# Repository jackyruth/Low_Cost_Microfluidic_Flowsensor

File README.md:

# Low Cost Flowsensor
https://github.com/jackyruth/Low_Cost_Microfluidic_Flowsensor/assets/32418878/434e1281-520d-4bf3-973c-ca0241b3b97c

## Description
- Does the Job! Measures up to 80 uL/min
- Cheap! Has a BOM cost < 30CAD
- Accurate! 5% Median Accuracy < 55 uL/min, 10-18% Median Accuracy > 55uL/min
- Non-invasive! Wet components are standard 1/32' OD tygon tubing and 29G stainless steel
- Simple Interface! UART Outputs every 15 seconds

This project is also well documented:
- 'Flowsensor Product Specification.pdf': Datasheet for the flowsensor
- 'Flowsensor Requirements, Design & Verification.pdf': A document describing the requirements, design and verification of the flowsensor
- 'flowsensor_demonstration.MOV': A video showing the benchmarking process
- 'UBC_BioMEMS_Product_Video.mp4': A video describing the context of the system the flowsensor is originally designed to be a part of.

## Project Tree
```
.
├── data
├── julia
├── lsi_lab_validation
├── pcb_v1
├── README.md
├── reagent_compatibility
└── stm32
```

- 'data' contains time series temperature data measured at set flow rates
- 'julia' contains data science Pluto notebooks used to experiment with the time series temperature data and analyze benchmarking data 
- 'lsi_lab_validation' contains the benchmarking data where we pitted the low cost sensor against the Sensirion SLI-0430 FMK flowsensor
- 'pcb_v1' contains a KiCAD PCB project of the flowsensor
- 'reagent_compatibility' contains benchmarking data where we ran different reagents, some at different temperatures, through the flowsensor
- 'stm32' contains the firmware for the flowsensor

# License
The hardware design is licensed under CERN-OHL-P-2.0. All other components are licensed under Apache-2.0.

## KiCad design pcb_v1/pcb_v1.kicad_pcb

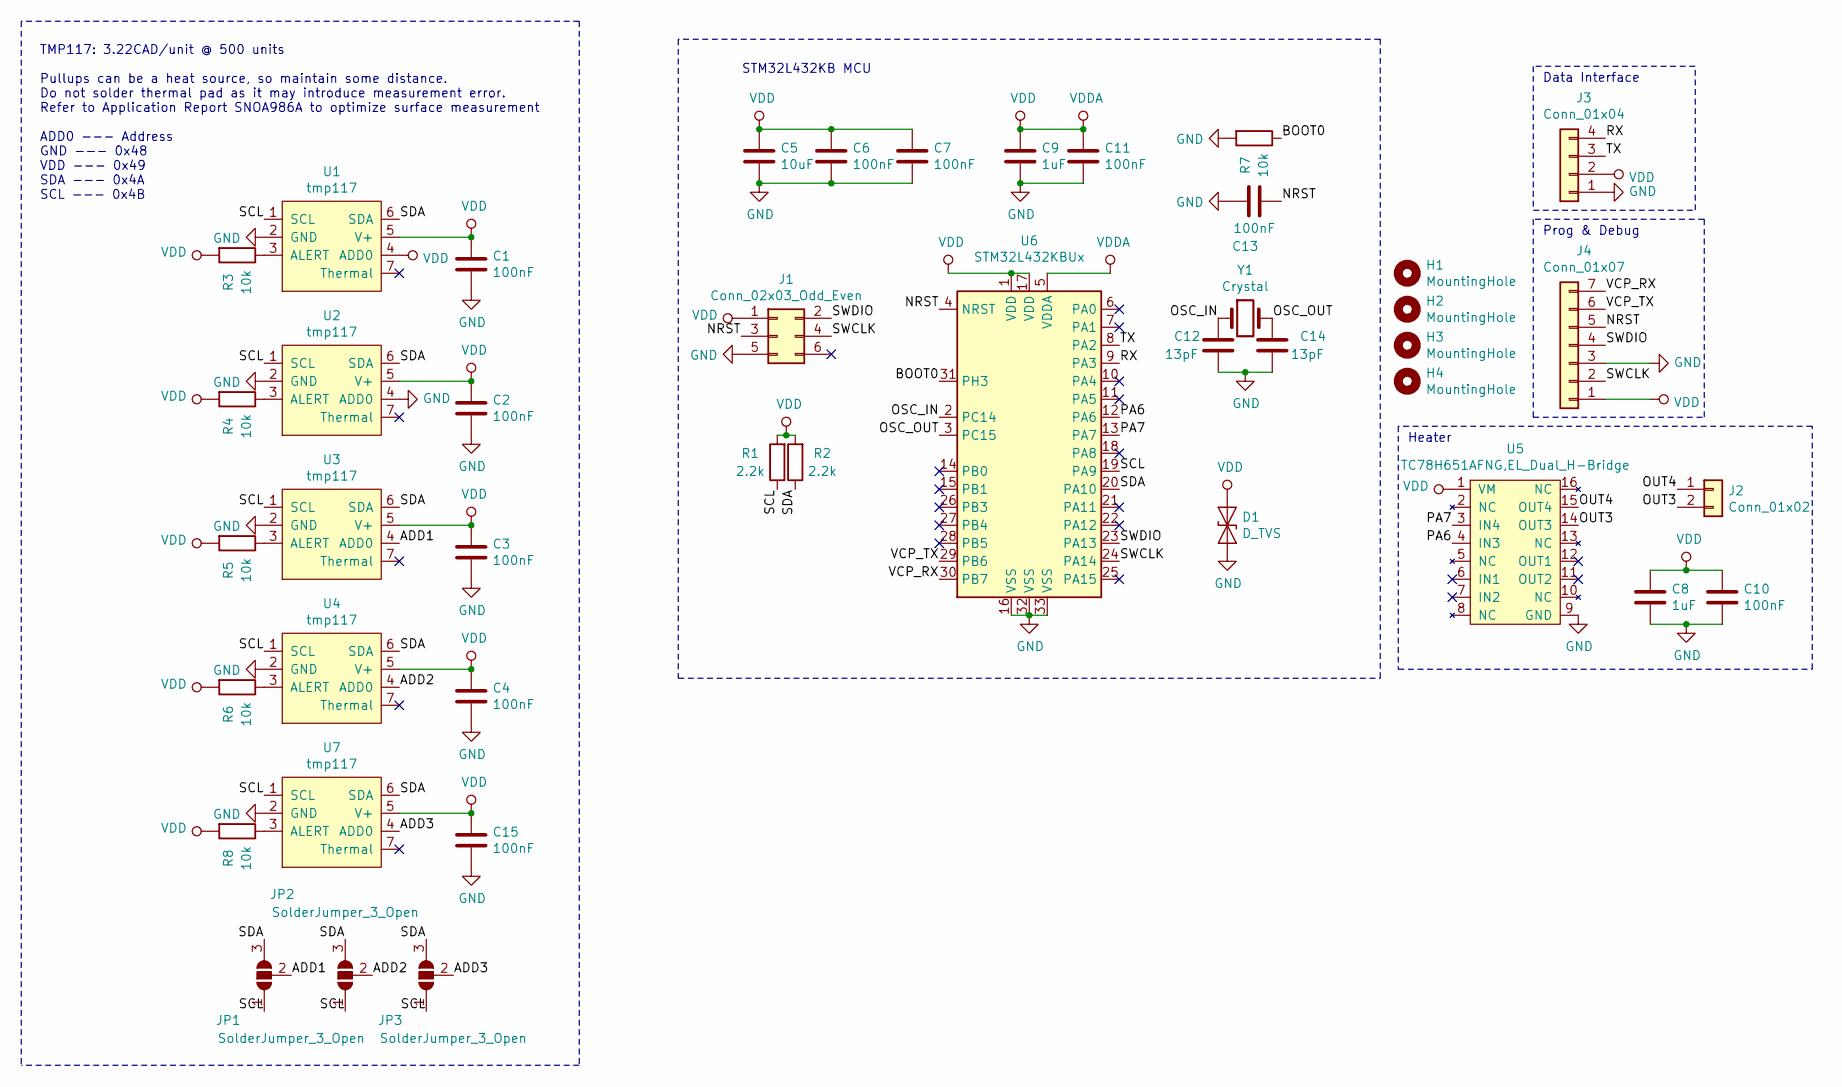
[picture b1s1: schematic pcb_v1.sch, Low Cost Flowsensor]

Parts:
C1, C2, C3, C4, C6, C7, C10, C11, C13, C15: 100nF; C_0603_1608Metric
C5: 10uF; C_0603_1608Metric
C8, C9: 1uF; C_0603_1608Metric
C12, C14: 13pF; C_0603_1608Metric
D1: D_TVS; D_SMA
H1, H2, H3, H4: MountingHole; MountingHole_2.2mm_M2
J1: Conn_02x03_Odd_Even; Tag-Connect_TC2030-IDC-NL_2x03_P1.27mm_Vertical
J2: Conn_01x02; R_Box_L8.4mm_W2.5mm_P5.08mm
J3: Conn_01x04; PinHeader_1x04_P2.54mm_Vertical
J4: Conn_01x07; PinHeader_1x07_P2.54mm_Vertical
JP1, JP2, JP3: SolderJumper_3_Open; SolderJumper-3_P1.3mm_Open_RoundedPad1.0x1.5mm_NumberLabels
R1, R2: 2.2k; C_0603_1608Metric
R3, R4, R5, R6, R7, R8: 10k; C_0603_1608Metric
U1, U2, U3, U4, U7: tmp117; THERMAL_ENHANCED_WSON-6-1EP_2x2mm_P0.65mm_EP1x1.6mm
U5: TC78H651AFNG,EL_Dual_H-Bridge
U6: STM32L432KBUx; QFN-32-1EP_5x5mm_P0.5mm_EP3.45x3.45mm
Y1: Crystal; ECS-.327-12.5-12R-C-TR

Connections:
/ADD1: JP1.2 (C), U3.4 (ADD0)
/ADD2: JP2.2 (C), U4.4 (ADD0)
/ADD3: JP3.2 (C), U7.4 (ADD0)
/BOOT0: R7.1, U6.31 (PH3)
/NRST: C13.2, J1.3, J4.5, U6.4 (NRST)
/OSC_IN: C12.2, U6.2 (PC14), Y1.1
/OSC_OUT: C14.2, U6.3 (PC15), Y1.2
/OUT3: J2.2, U5.14 (OUT3)
/OUT4: J2.1, U5.15 (OUT4)
/PA6: U5.4 (IN3), U6.12 (PA6)
/PA7: U5.3 (IN4), U6.13 (PA7)
/RX: J3.4, U6.9 (PA3)
/SCL: JP1.1 (A), JP2.1 (A), JP3.1 (A), R1.1, U1.1 (SCL), U2.1 (SCL), U3.1 (SCL), U4.1 (SCL), U6.19 (PA9), U7.1 (SCL)
/SDA: JP1.3 (B), JP2.3 (B), JP3.3 (B), R2.1, U1.6 (SDA), U2.6 (SDA), U3.6 (SDA), U4.6 (SDA), U6.20 (PA10), U7.6 (SDA)
/SWCLK: J1.4, J4.2, U6.24 (PA14)
/SWDIO: J1.2, J4.4, U6.23 (PA13)
/TX: J3.3, U6.8 (PA2)
/VCP_RX: J4.7, U6.30 (PB7)
/VCP_TX: J4.6, U6.29 (PB6)
GND: C1.1, C2.1, C3.1, C4.1, C5.2, C6.2, C7.2, C8.2, C9.2, C10.2, C11.2, C12.1, C13.1, C14.1, C15.1, D1.2 (A2), J1.5, J3.1, J4.3, R7.2, U1.2 (GND), U2.2 (GND), U2.4 (ADD0), U3.2 (GND), U4.2 (GND), U5.9 (GND), U6.16 (VSS), U6.32 (VSS), U6.33 (VSS), U7.2 (GND)
unnamed: R3.1, U1.3 (ALERT)
unnamed: R4.1, U2.3 (ALERT)
unnamed: R5.1, U3.3 (ALERT)
unnamed: R6.1, U4.3 (ALERT)
unnamed: R8.1, U7.3 (ALERT)
VDD: C1.2, C2.2, C3.2, C4.2, C5.1, C6.1, C7.1, C8.1, C9.1, C10.1, C11.1, C15.2, D1.1 (A1), J1.1, J3.2, J4.1, R1.2, R2.2, R3.2, R4.2, R5.2, R6.2, R8.2, U1.4 (ADD0), U1.5 (V+), U2.5 (V+), U3.5 (V+), U4.5 (V+), U5.1 (VM), U6.1 (VDD), U6.5 (VDDA), U6.17 (VDD), U7.5 (V+)

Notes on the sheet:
TMP117: 3.22CAD/unit @ 500 units Pullups can be a heat source, so maintain some distance. Do not solder thermal pad as it may introduce measurement error. Refer to Application Report SNOA986A to optimize surface measurement ADD0 --- Address GND --- 0x48 VDD --- 0x49 SDA --- 0x4A SCL --- 0x4B
STM32L432KB MCU
Prog & Debug
Data Interface
Heater

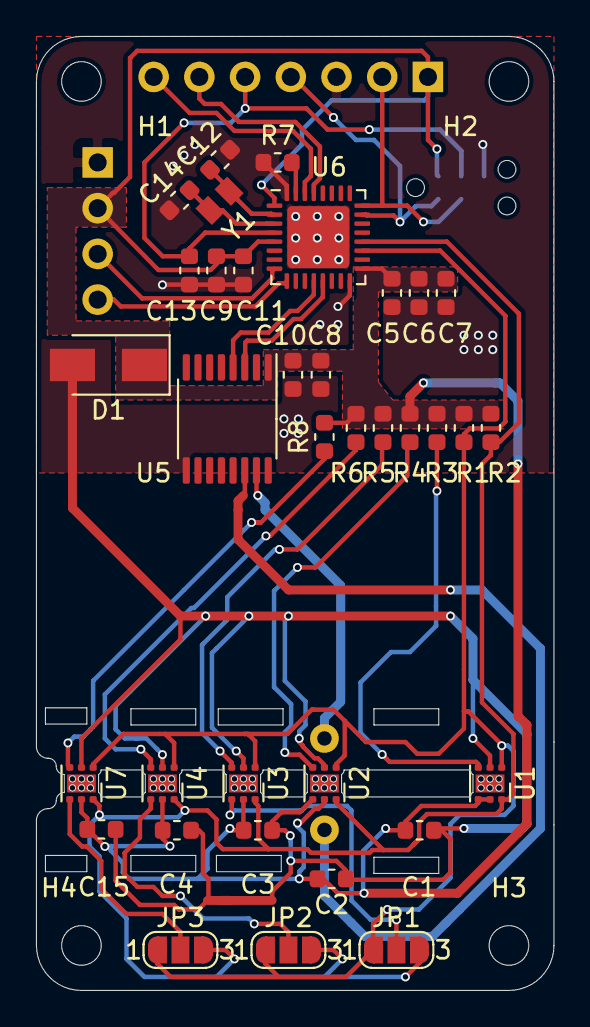
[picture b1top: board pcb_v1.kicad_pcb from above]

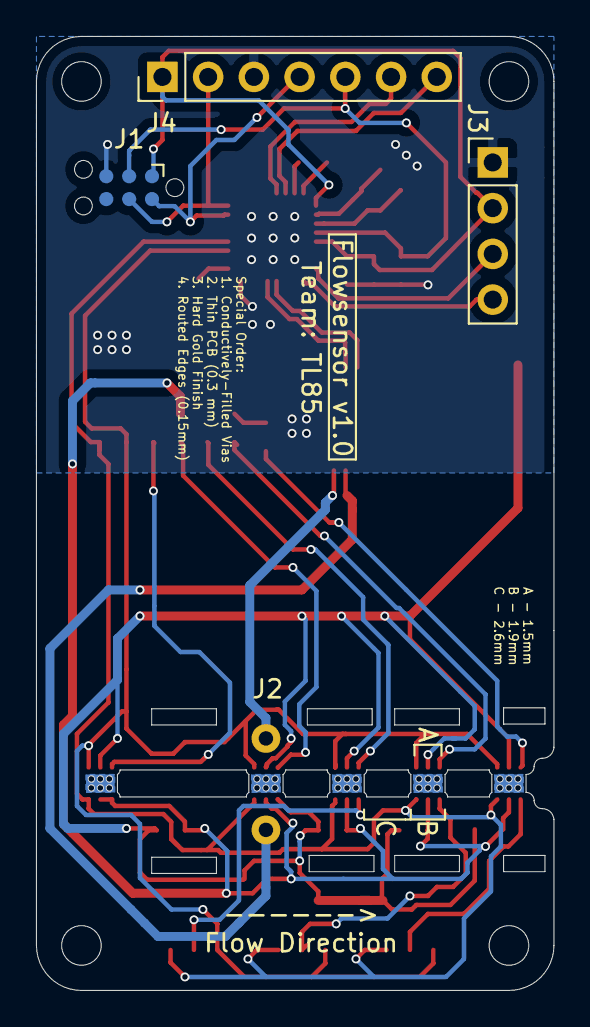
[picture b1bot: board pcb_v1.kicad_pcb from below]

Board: 2 copper layers, 28.8 x 53.0 mm, 43 parts (4 on the bottom side), 26 nets.

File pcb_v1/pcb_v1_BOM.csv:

"Id";"Designator";"Package";"Quantity";"Designation";"Supplier and ref";
1;"G***";"ubc_logo";1;"LOGO";;;
2;"JP3,JP2,JP1";"SolderJumper-3_P1.3mm_Open_RoundedPad1.0x1.5mm_NumberLabels";3;"SolderJumper_3_Open";;;
3;"U7,U4,U3,U2,U1";"WSON-6-1EP_2x2mm_P0.65mm_EP1x1.6mm";5;"tmp117";;;
4;"R8,R7,R6,R5,R4,R3";"C_0603_1608Metric";6;"10k";;;
5;"C15,C13,C11,C10,C7,C6,C4,C3,C2,C1";"C_0603_1608Metric";10;"100nF";;;
6;"J2";"R_Box_L8.4mm_W2.5mm_P5.08mm";1;"Conn_01x02";;;
7;"H4,H3,H2,H1";"MountingHole_2.2mm_M2";4;"MountingHole";;;
8;"U5";"TC78H651AFNG,EL_Dual_H-Bridge";1;"TC78H651AFNG,EL_Dual_H-Bridge";;;
9;"Y1";"ECS-.327-12.5-12R-C-TR";1;"Crystal";;;
10;"U6";"QFN-32-1EP_5x5mm_P0.5mm_EP3.45x3.45mm";1;"STM32L432KBUx";;;
11;"J4";"PinHeader_1x07_P2.54mm_Vertical";1;"Conn_01x07";;;
12;"J3";"PinHeader_1x04_P2.54mm_Vertical";1;"Conn_01x04";;;
13;"J1";"Tag-Connect_TC2030-IDC-NL_2x03_P1.27mm_Vertical";1;"Conn_02x03_Odd_Even";;;
14;"D1";"D_SMA";1;"D_TVS";;;
15;"C14,C12";"C_0603_1608Metric";2;"13pF";;;
16;"C9,C8";"C_0603_1608Metric";2;"1uF";;;
17;"C5";"C_0603_1608Metric";1;"10uF";;;
18;"R2,R1";"C_0603_1608Metric";2;"2.2k";;;

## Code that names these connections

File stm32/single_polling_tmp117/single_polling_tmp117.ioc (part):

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Mcu.Name=STM32L432K(B-C)Ux
Mcu.Package=UFQFPN32
Mcu.UserName=STM32L432KBUx
PA0.GPIOParameters=GPIO_Label
PA0.GPIO_Label=MCO
PA0.Signal=RCC_CK_IN
PA10.Mode=I2C
PA10.Signal=I2C1_SDA
PA13\ (JTMS-SWDIO).GPIOParameters=GPIO_Label
PA13\ (JTMS-SWDIO).GPIO_Label=SWDIO
PA13\ (JTMS-SWDIO).Mode=Serial_Wire
PA13\ (JTMS-SWDIO).Signal=SYS_JTMS-SWDIO
PA14\ (JTCK-SWCLK).GPIOParameters=GPIO_Label
PA14\ (JTCK-SWCLK).GPIO_Label=SWCLK
PA14\ (JTCK-SWCLK).Mode=Serial_Wire
PA14\ (JTCK-SWCLK).Signal=SYS_JTCK-SWCLK
PA2.Mode=Asynchronous
PA2.Signal=LPUART1_TX
PA3.Mode=Asynchronous
PA3.Signal=LPUART1_RX
PA6.GPIOParameters=GPIO_PuPd
PA6.GPIO_PuPd=GPIO_PULLDOWN
PA6.Signal=GPIO_Output
PA7.GPIOParameters=GPIO_PuPd
PA7.GPIO_PuPd=GPIO_PULLDOWN
PA7.Signal=GPIO_Output
PA9.Mode=I2C
PA9.Signal=I2C1_SCL
PB0.Signal=GPIO_Output
PB6.Mode=Asynchronous
PB6.Signal=USART1_TX
PB7.Mode=Asynchronous
PB7.Signal=USART1_RX
PC14-OSC32_IN\ (PC14).Mode=LSE-External-Oscillator
PC14-OSC32_IN\ (PC14).Signal=RCC_OSC32_IN
PC15-OSC32_OUT\ (PC15).Mode=LSE-External-Oscillator
PC15-OSC32_OUT\ (PC15).Signal=RCC_OSC32_OUT
RCC.HSE_VALUE=8000000
RCC.SYSCLKFreq_VALUE=48000000
board=custom

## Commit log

2021-12-15 Uploaded initial capstone code
2022-01-09 Working double sensor
2022-01-16 more intuitive time tune
2022-01-16 Added single sensor code
2022-01-17 Added PCB and data
2022-01-17 added math model and ability to segment
2022-01-17 Updated graphs
2022-01-17 Sample model
2022-01-18 Added data and updated analysis programs
2022-01-18 Added Data Ready
2022-01-19 added arduino code and confirmed that glitch is caused by zephyr
2022-01-19 Added data
2022-01-19 Changed segmentation to read from yml file
2022-01-20 added cubeide code
2022-01-20 Updated PCB w extra position
2022-01-23 updated PCB files
2022-01-23 Added stm32cubeide code
2022-01-23 Cleaned repo and added julia code
2022-01-24 Working human tuning sliders & non-linear least squares
2022-01-25 Extracted the important variables
2022-01-27 Added statistical analysis
2022-01-27 Completed data analysis and figured out how to convert temperature data to flowrate
2022-02-06 Added working levenberg implementation
2022-02-06 Successfully getting timedelta from temperature data
2022-02-06 Added more data to working timedelta example
2022-02-07 Added data_collection firmware, currently only quickly polls from a single sensor
2022-02-08 Added pcb data
2022-02-08 Added far sensor data
2022-02-10 Added functional firmware
2022-02-10 deleted superfluous code
2022-02-10 refactored data location
2022-02-10 Finalized flowsensor project
2022-02-14 Moved BOM file to root directory
2022-03-18 updated with lab data
2022-03-18 Updated lab data and procedure
2022-03-19 cleaned repo
2022-03-19 Cleaned up repo
2022-03-19 Added documentation
2022-03-20 Completed benchmarking data analysis
2022-03-20 Added flow rate sensor product spec
2022-03-24 Corrected units in benchmarking
2022-03-24 Finished product datasheet
2022-03-29 Updated documentation and added more benchmarking results
2022-03-29 Added demo video
2022-03-29 Added Product Video
2022-03-29 Edited README.md
2022-05-11 Added generated gerber file
2024-01-09 updated with annotated video
